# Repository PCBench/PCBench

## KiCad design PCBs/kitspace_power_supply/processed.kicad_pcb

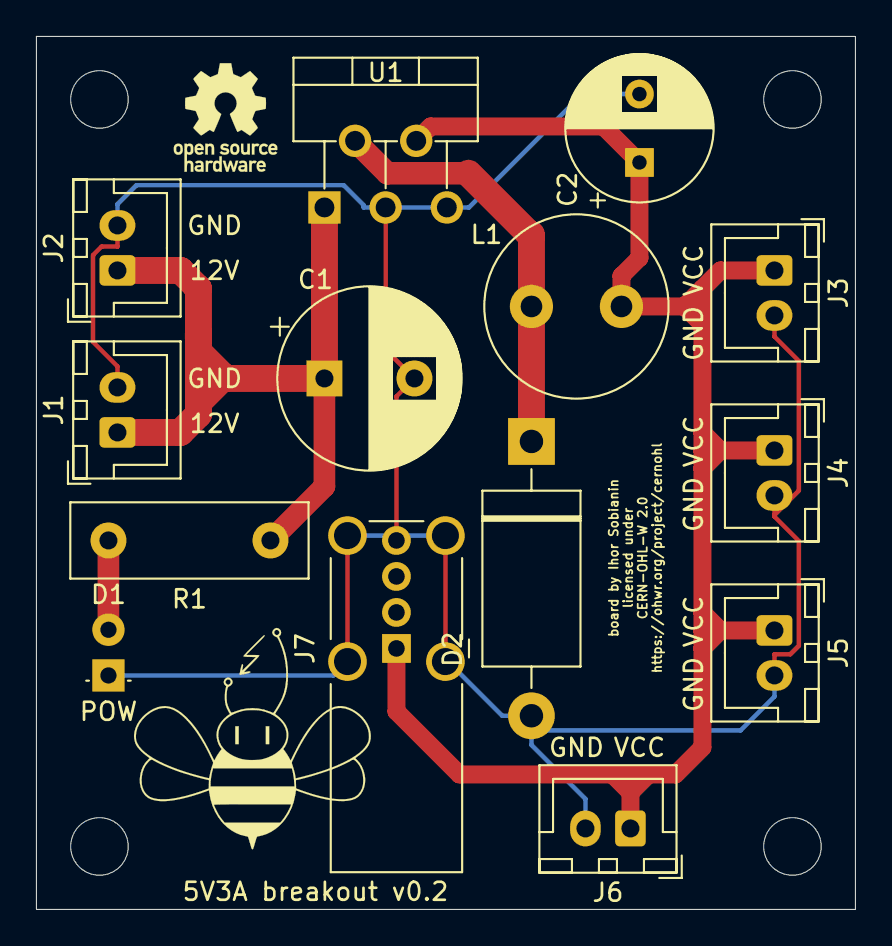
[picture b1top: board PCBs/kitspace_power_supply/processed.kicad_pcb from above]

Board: 2 copper layers, 45.5 x 48.5 mm, 19 parts (0 on the bottom side), 5 nets.

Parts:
C1: 680µ; CP_Radial_D10.0mm_P5.00mm
C2: 220µ; CP_Radial_D8.0mm_P3.80mm
D1: LED; LED_D3.0mm
D2: D_Schottky; D_DO-201_P15.24mm_Horizontal
J1, J2, J3, J4, J5, J6: Conn_01x02; JST_XH_B2B-XH-A_1x02_P2.50mm_Vertical
J7: USB_A; USB_A_Wuerth_614004134726_Horizontal
L1: 33µH; L_Radial_D10.0mm_P5.00mm_Neosid_SD12_style3
R1: 560; R_Box_L13.0mm_W4.0mm_P9.00mm
REF1, REF2, REF3, REF4: MountingHole_3.2mm_M3_DIN965
REF5: OSHW-Logo_5.7x6mm_SilkScreen
U1: LM2596S-5; TO-220-5_P3.4x3.7mm_StaggerOdd_Lead3.8mm_Vertical

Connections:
GND: C1.2, C2.2, D1.1, D2.2, J1.2, J2.2, J3.2, J4.2, J5.2, J6.2, J7.4, J7.5, U1.3, U1.5
unnamed: C1.1, J1.1, J2.1, R1.1, U1.1
unnamed: C2.1, J3.1, J4.1, J5.1, J6.1, J7.1, L1.2, U1.4
unnamed: D1.2, R1.2
unnamed: D2.1, L1.1, U1.2

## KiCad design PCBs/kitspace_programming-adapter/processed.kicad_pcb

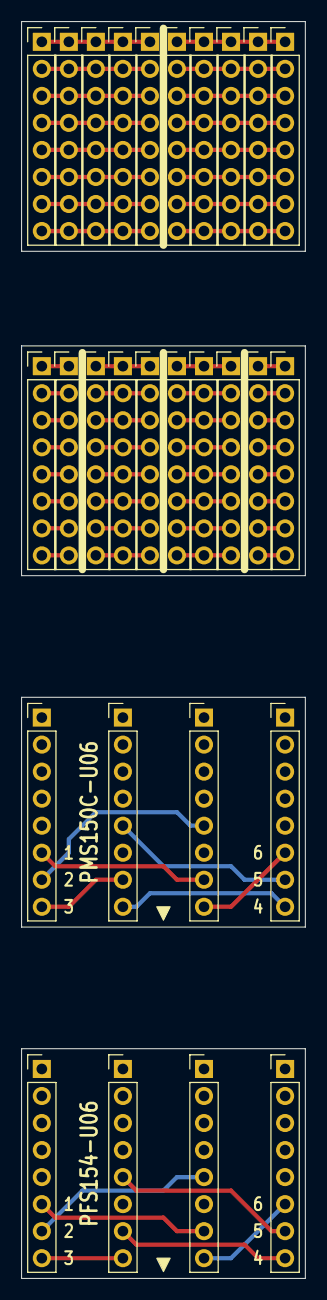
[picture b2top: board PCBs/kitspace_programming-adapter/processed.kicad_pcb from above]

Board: 2 copper layers, 26.7 x 118.1 mm, 28 parts (0 on the bottom side), 60 nets.

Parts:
J1, J2, J3, J4, J5, J6, J7, J8, J9, J10, J11, J12, J13, J14, J15, J16, J17, J18, J19, J20, J21, J22, J23, J24, J25, J26, J27, J28: Conn_01x08; PinHeader_1x08_P2.54mm_Vertical

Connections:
/GND1: J21.7, J25.5
/GND2: J22.7, J26.5
/ICPCK1: J25.8, J27.6
/ICPCK2: J26.8, J28.6
/ICPDA1: J21.8, J23.7
/ICPDA2: J24.7, J28.8
/MOSI: J21.6, J25.7
/PA4: J22.6, J26.7
/VPP1: J23.8, J27.8
/Vdd1: J23.5, J27.7
/Vdd2: J24.5, J28.7
/Vpp2: J22.8, J24.8
unnamed: J1.1, J3.1
unnamed: J1.2, J3.2
unnamed: J1.3, J3.3
unnamed: J1.4, J3.4
unnamed: J1.5, J3.5
unnamed: J1.6, J3.6
unnamed: J1.7, J3.7
unnamed: J1.8, J3.8
unnamed: J2.1, J4.1, J9.1
unnamed: J2.2, J9.2
unnamed: J2.3, J9.3
unnamed: J2.4, J9.4
unnamed: J2.5, J9.5
unnamed: J2.6, J7.6, J9.6
unnamed: J2.7, J9.7
unnamed: J2.8, J9.8
unnamed: J6.1, J10.1
unnamed: J6.2, J10.2
unnamed: J6.3, J10.3
unnamed: J6.4, J10.4
unnamed: J6.5, J10.5
unnamed: J6.6, J10.6
unnamed: J6.7, J10.7
unnamed: J6.8, J10.8
unnamed: J11.1, J19.1
unnamed: J11.2, J19.2
unnamed: J11.3, J19.3
unnamed: J11.4, J19.4
unnamed: J11.5, J19.5
unnamed: J11.6, J19.6
unnamed: J11.7, J19.7
unnamed: J11.8, J19.8
unnamed: J12.1, J16.1
unnamed: J12.2, J16.2
unnamed: J12.3, J16.3
unnamed: J12.4, J16.4
unnamed: J12.5, J16.5
unnamed: J12.6, J16.6
unnamed: J12.7, J16.7
unnamed: J12.8, J16.8
unnamed: J18.1, J20.1
unnamed: J18.2, J20.2
unnamed: J18.3, J20.3
unnamed: J18.4, J20.4
unnamed: J18.5, J20.5
unnamed: J18.6, J20.6
unnamed: J18.7, J20.7
unnamed: J18.8, J20.8

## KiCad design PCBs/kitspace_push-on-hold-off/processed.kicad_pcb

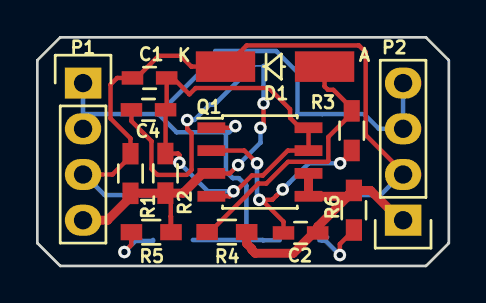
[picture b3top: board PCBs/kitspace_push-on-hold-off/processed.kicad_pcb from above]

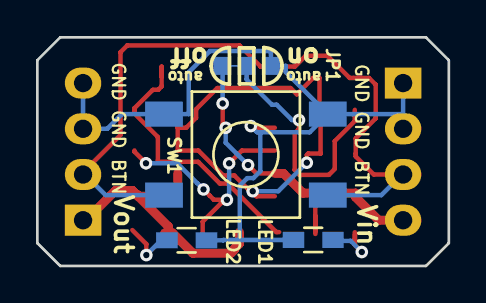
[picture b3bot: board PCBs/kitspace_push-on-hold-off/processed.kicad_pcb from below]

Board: 2 copper layers, 22.9 x 12.7 mm, 17 parts (4 on the bottom side), 9 nets.

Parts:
C1: 1uF; C_0603_HandSoldering
C2: 10uF; C_0603_HandSoldering
C4: 0.1uF; C_0603_HandSoldering
D1: D; MiniMELF_Handsoldering
JP1: JUMPER3; SOLDER-JUMPER_2-WAY
LED1, LED2: LED; R_0603_HandSoldering
P1, P2: CONN_01X04; Pin_Header_Straight_1x04
Q1: IRF7309IPBF; SOIC-8_3.9x4.9mm_Pitch1.27mm
R1: 10k; R_0603_HandSoldering
R2, R4: 100k; R_0603_HandSoldering
R3: 300k; R_0603_HandSoldering
R5, R6: 1k; R_0603_HandSoldering
SW1: SW_PUSH_SMALL; FSM2JSMA

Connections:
/Button: C1.2, D1.1, P1.3, P2.2, R1.2, SW1.1
/Vin: C4.1, JP1.2, JP1.3, P1.4, Q1.3, R1.1, R2.1, R5.1
/Vout: C2.2, P2.1, Q1.5, Q1.6, R4.1, R6.1
GND: JP1.1, LED1.1, LED2.1, P1.1, P1.2, P2.3, P2.4, Q1.1, SW1.2
unnamed: C1.1, C4.2, Q1.4, Q1.7, Q1.8, R2.2
unnamed: C2.1, Q1.2, R3.2
unnamed: D1.2, R3.1, R4.2
unnamed: LED1.2, R5.2
unnamed: LED2.2, R6.2

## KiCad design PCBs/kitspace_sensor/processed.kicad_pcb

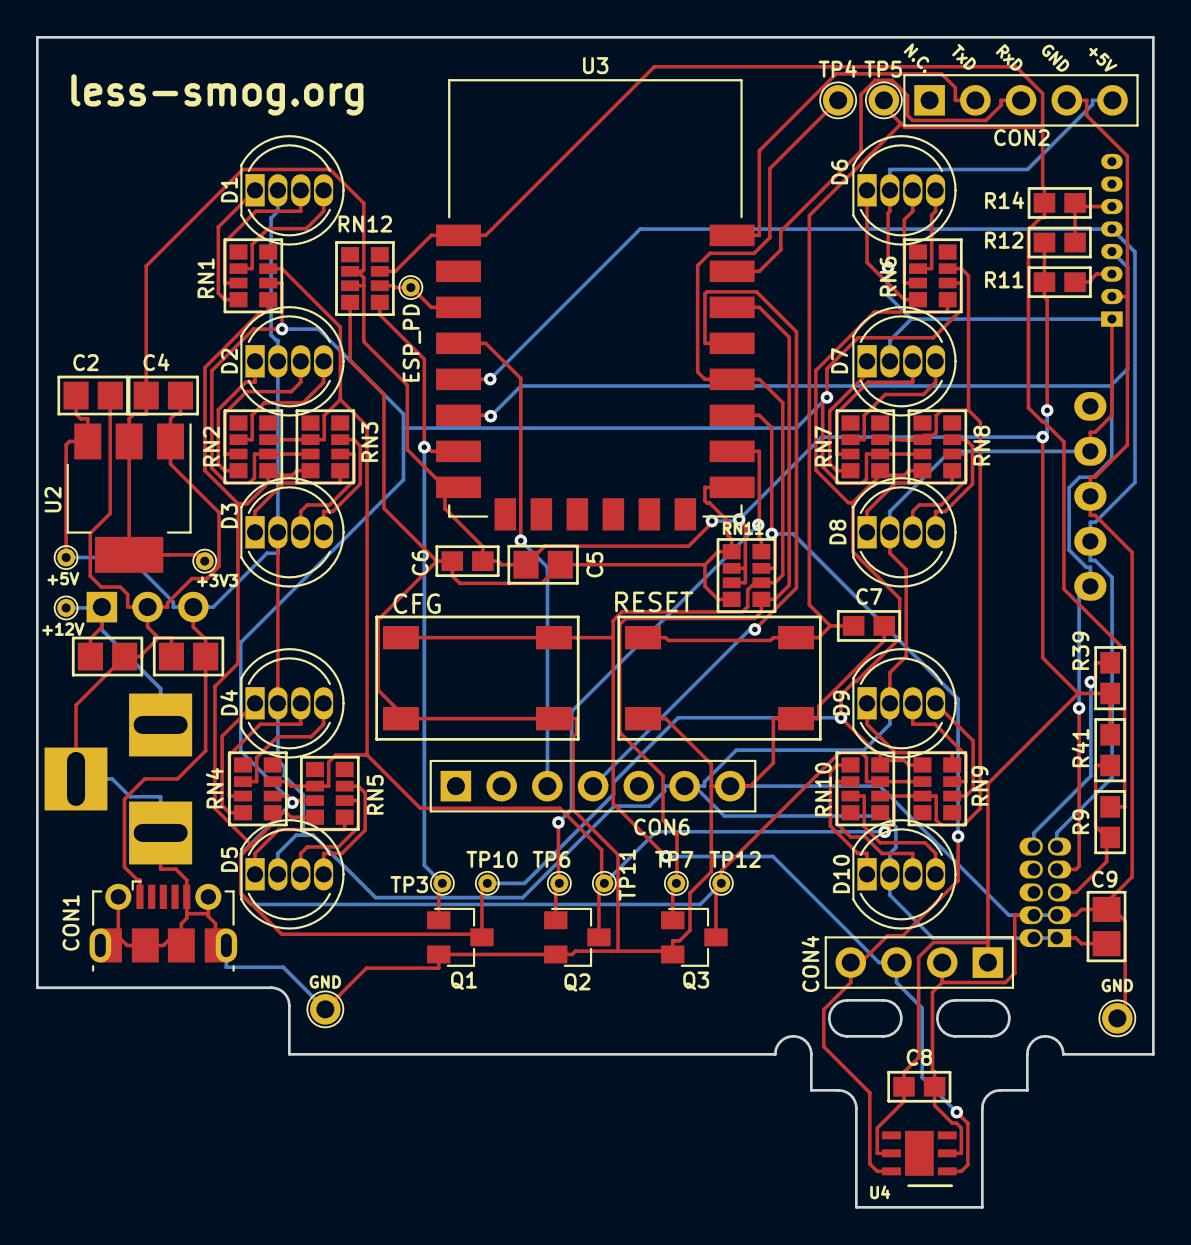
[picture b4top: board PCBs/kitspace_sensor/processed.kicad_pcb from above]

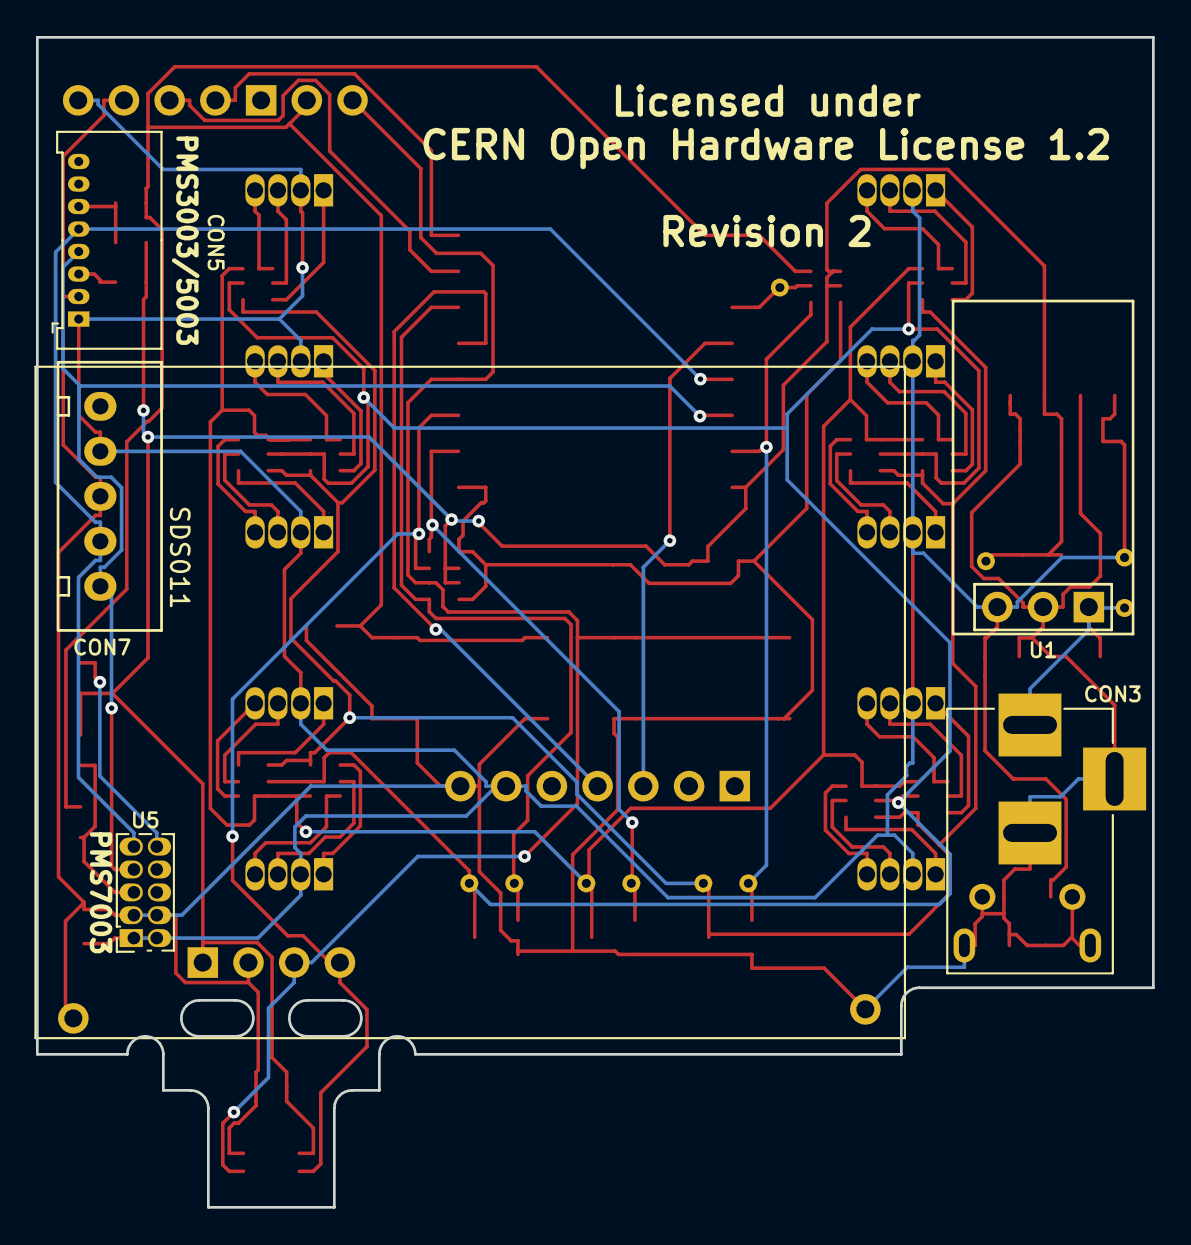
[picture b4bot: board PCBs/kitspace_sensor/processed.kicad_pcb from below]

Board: 2 copper layers, 62.0 x 65.0 mm, 68 parts (5 on the bottom side), 54 nets.

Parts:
C1, C3: N.C.; 0805_M
C2, C4, C5, C9: 10uF/10V; 0805_M
C6, C7, C8: 100nF; 0603_M
CON1: Micro USB; USB_Micro-B_Molex-105017-0001
CON2: PROG; Pin_Header_Straight_1x05_Pitch2.54mm
CON3: N.C.; BARREL_JACK
CON4: HTU21D; HTU21D_module
CON5: PMS3003/5003; Molex_PicoBlade_53048-0810
CON6: AUX; E45-TTL-1W
CON7: SDS011; B5B-XH-A(LF)(SN)
D1, D2, D3, D4, D5, D6, D7, D8, D9, D10: RGB 5mm; LED_D5.0mm-4
Q1, Q2, Q3: BSS214N; SOT-23
R9, R11, R12, R14: N.C.; 0603_R_M
R39, R41: 10k; 0603_R_M
RN1, RN2, RN3, RN4, RN5, RN6, RN7, RN8, RN9, RN10: 150R; 4x0603_M
RN11, RN12: 10k; 4x0603_M
SW1: RESET; MicroswitchSmd-4.3_N
SW2: CFG; MicroswitchSmd-4.3_N
TP1: ESP_PD; TP_1.0_0.5_THT
TP2, TP14: GND; TP_1.7_1.0_THT
TP3, TP6, TP7, TP10, TP11, TP12: -; TP_1.0_0.5_THT
TP4: CFG; TP_1.7_1.0_THT
TP5: RESET; TP_1.7_1.0_THT
TP8: +5V; TP_1.0_0.5_THT
TP9: +12V; TP_1.0_0.5_THT
TP13: +3V3; TP_1.0_0.5_THT
U1: N.C.; 5V_DC_DC
U2: TLV1117LV33DCY; SOT-223-3Lead_TabPin2
U3: ESP-12F
U4: HTU21D
U5: PMS7003; PMS7003_THT

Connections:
+3V3: C4.1, C5.1, C6.1, C8.1, CON4.1, R11.2, R12.2, R39.1, R41.1, RN11.2, RN11.3, RN12.2, RN12.3, TP13.1, U2.2, U3.8, U4.5
+5V: C2.1, C3.1, C9.1, CON1.1, CON2.5, CON5.1, CON6.6, CON7.4, D1.2, D2.2, D3.2, D4.2, D5.2, D6.2, D7.2, D8.2, D9.2, D10.2, TP8.1, U1.3, U2.3, U5.1, U5.2
+12V: C1.1, CON3.1, TP9.1, U1.1
/ESP_PD: RN12.6, TP1.1, U3.3
/LED_B: Q3.3, RN1.2, RN2.2, RN3.7, RN4.2, RN5.7, RN6.2, RN7.2, RN8.7, RN9.2, RN10.7, TP12.1
/LED_G: Q2.3, RN1.3, RN2.3, RN3.6, RN4.3, RN5.6, RN6.3, RN7.3, RN8.6, RN9.3, RN10.6, TP11.1
/LED_R: Q1.3, RN1.1, RN2.1, RN3.8, RN4.1, RN5.8, RN6.1, RN7.1, RN8.8, RN9.1, RN10.8, TP10.1
ESP_RXD: CON2.3, U3.21
ESP_TXD: CON2.2, U3.22
GND: C1.2, C2.2, C3.2, C4.2, C5.2, C6.2, C7.2, C8.2, C9.2, CON1.5, CON1.6, CON2.4, CON3.2, CON3.3, CON4.2, CON5.2, CON6.7, CON7.3, Q1.2, Q2.2, Q3.2, RN11.1, RN11.4, RN12.4, SW1.2, SW2.2, TP2.1, TP14.1, U1.2, U2.1, U3.15, U4.2, U5.3, U5.4
GPIO4: CON6.4, U3.19
GPIO16: CON6.3, U3.4
HTU_SCL: CON4.4, RN11.7, U3.17, U4.6
HTU_SDA/CFG_BTN: CON4.3, RN11.6, SW2.1, TP4.1, U3.18, U4.1
LED_B_CTRL: Q3.1, RN11.5, TP7.1, U3.20
LED_G_CTRL: Q2.1, RN11.8, TP6.1, U3.16
LED_R_CTRL: Q1.1, RN12.5, TP3.1, U3.7
unnamed: CON5.3, R11.1
unnamed: CON5.6, R12.1, R14.1
unnamed: D1.1, RN1.8
unnamed: D1.3, RN1.7
unnamed: D1.4, RN1.6
unnamed: D2.1, RN2.8
unnamed: D2.3, RN2.7
unnamed: D2.4, RN2.6
unnamed: D3.1, RN3.1
unnamed: D3.3, RN3.2
unnamed: D3.4, RN3.3
unnamed: D4.1, RN4.8
unnamed: D4.3, RN4.7
unnamed: D4.4, RN4.6
unnamed: D5.1, RN5.1
unnamed: D5.3, RN5.2
unnamed: D5.4, RN5.3
unnamed: D6.1, RN6.8
unnamed: D6.3, RN6.7
unnamed: D6.4, RN6.6
unnamed: D7.1, RN7.8
unnamed: D7.3, RN7.7
unnamed: D7.4, RN7.6
unnamed: D8.1, RN8.1
unnamed: D8.3, RN8.2
unnamed: D8.4, RN8.3
unnamed: D9.1, RN9.8
unnamed: D9.3, RN9.7
unnamed: D9.4, RN9.6
unnamed: D10.1, RN10.1
unnamed: D10.3, RN10.2
unnamed: D10.4, RN10.3
unnamed: R39.2, U5.10
unnamed: R9.1, R41.2, U5.5
PMS_RXD: CON5.4, CON7.1, U3.6, U5.7
PMS_TXD: CON5.5, CON7.2, U3.5, U5.9
RESET: C7.1, R9.2, R14.2, RN12.7, SW1.1, TP5.1, U3.1

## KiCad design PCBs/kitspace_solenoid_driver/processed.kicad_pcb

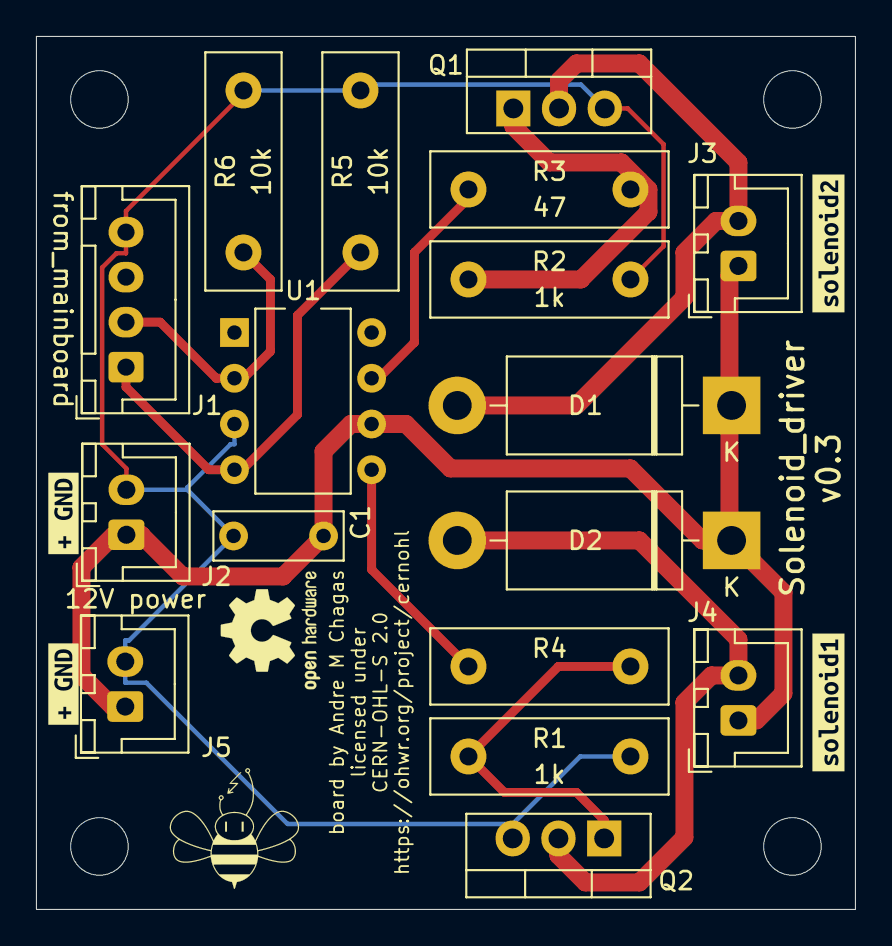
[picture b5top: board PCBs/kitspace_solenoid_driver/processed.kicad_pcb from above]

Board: 2 copper layers, 45.5 x 48.5 mm, 26 parts (0 on the bottom side), 10 nets.

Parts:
C1: 100nF; C_Disc_D7.0mm_W2.5mm_P5.00mm
D1, D2: D_Schottky; D_DO-201AD_P15.24mm_Horizontal
J1: from_mainboard; JST_XH_B4B-XH-A_1x04_P2.50mm_Vertical
J2, J5: 12V power; JST_XH_B2B-XH-A_1x02_P2.50mm_Vertical
J3: to_solenoid2; JST_XH_B2B-XH-A_1x02_P2.50mm_Vertical
J4: to_solenoid1; JST_XH_B2B-XH-A_1x02_P2.50mm_Vertical
Q1, Q2: Q_NMOS_GDS; TO-220-3_Vertical
R1, R2: 1k; R_Box_L13.0mm_W4.0mm_P9.00mm
R3, R4: 47; R_Box_L13.0mm_W4.0mm_P9.00mm
R5, R6: 10k; R_Box_L13.0mm_W4.0mm_P9.00mm
REF1, REF2, REF3, REF4: MountingHole_3.2mm_M3_DIN965
REF5: OSHW-Logo2_7.3x6mm_SilkScreen
U1: MIC4427; DIP-8_W7.62mm
kibuzzard-63063C94: G***; kibuzzard-63063C94
kibuzzard-63064E8E: G***; kibuzzard-63064E8E
kibuzzard-63064EFA: G***; kibuzzard-63064EFA
kibuzzard-63065932: G***; kibuzzard-63065932

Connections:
+12V: C1.1, D1.1, D2.1, J2.1, J3.1, J4.1, J5.1, U1.6
GND: C1.2, J1.4, J2.2, J5.2, Q1.3, Q2.3, R1.1, R2.1, R5.1, R6.1, U1.3
unnamed: D1.2, J3.2, Q1.2
unnamed: D2.2, J4.2, Q2.2
unnamed: J1.1, R5.2, U1.4
unnamed: Q1.1, R2.2, R3.1
unnamed: Q2.1, R1.2, R4.1
unnamed: J1.2, R6.2, U1.2
solenoid1: R3.2, U1.7
solenoid2: R4.2, U1.5

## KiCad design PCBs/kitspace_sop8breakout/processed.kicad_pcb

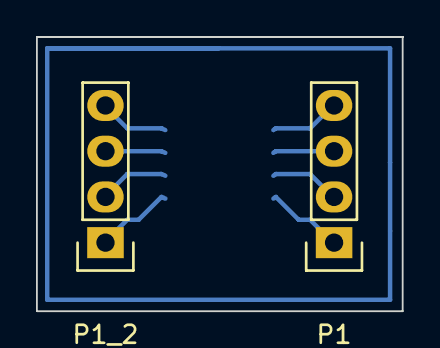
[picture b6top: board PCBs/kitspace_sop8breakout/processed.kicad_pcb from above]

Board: 2 copper layers, 20.3 x 15.2 mm, 3 parts (1 on the bottom side), 8 nets.

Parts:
IC1: MCP6002; SOP-8
P1, P1_2: CONN_01X04; Pin_Header_Straight_1x04

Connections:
unnamed: IC1.1, P1_2.1
unnamed: IC1.2, P1_2.2
unnamed: IC1.3, P1_2.3
unnamed: IC1.4, P1_2.4
unnamed: IC1.5, P1.4
unnamed: IC1.6, P1.3
unnamed: IC1.7, P1.2
unnamed: IC1.8, P1.1

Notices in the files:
PCBs/kitspace_power_supply/processed.kicad_pcb:
licensed under
CERN-OHL-W 2.0
PCBs/kitspace_sensor/processed.kicad_pcb:
CERN Open Hardware License 1.2
PCBs/kitspace_solenoid_driver/processed.kicad_pcb:
CERN-OHL-S 2.0
